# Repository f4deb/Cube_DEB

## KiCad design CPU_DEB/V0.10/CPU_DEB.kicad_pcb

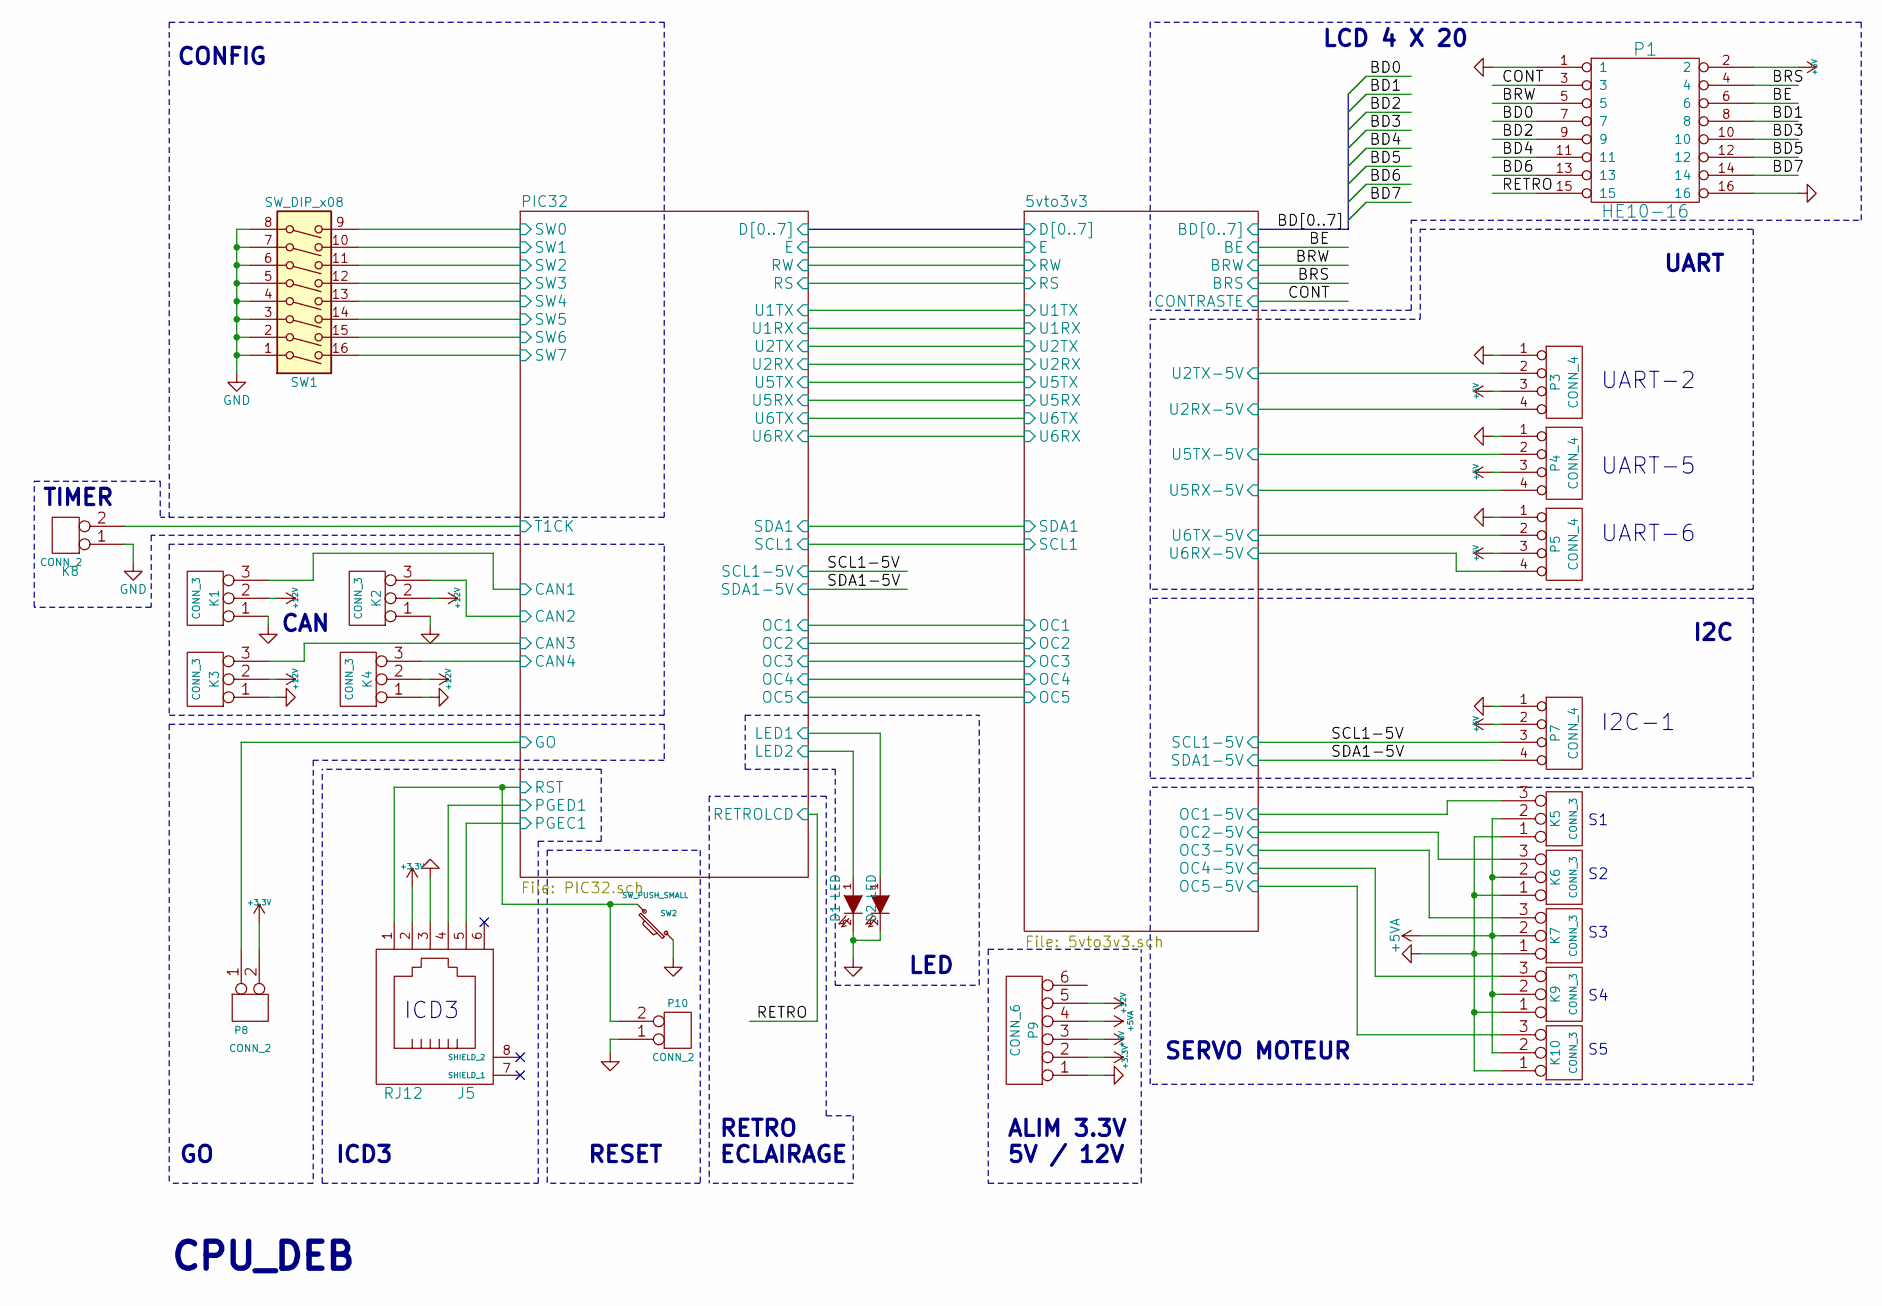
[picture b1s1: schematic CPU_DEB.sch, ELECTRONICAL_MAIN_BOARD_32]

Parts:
D1, D2: LED; LED_0603
J5: RJ12
K1, K2, K3, K4: CONN_3; KK-3
K5, K6, K7, K9, K10: CONN_3; KK-3-H
K8: CONN_2; KK-2-H
P1: HE10-16; he10-16d
P3: CONN_4; Molex_KK_6410-04
P4, P5, P7: CONN_4; KK-4-H
P8, P10: CONN_2; KK-2-H
P9: CONN_6; KK-6-H
SW1: SW_DIP_x08; SW_DIP_x8_Piano
SW2: SW_PUSH_SMALL; SW

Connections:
+3V3: J5.2, P8.2 (PM), P9.2; also elsewhere on the board
+5V: P1.2, P3.3, P4.3, P5.3, P7.2, P9.3; also elsewhere on the board
+5VA: K5.2 (PM), K6.2 (PM), K7.2 (PM), K9.2 (PM), K10.2 (PM), P9.4; also elsewhere on the board
+12V: K1.2 (PM), K2.2 (PM), K3.2 (PM), K4.2 (PM), P9.5
/5vto3v3/OC1-5V: K5.3; also elsewhere on the board
/5vto3v3/OC2-5V: K6.3; also elsewhere on the board
/5vto3v3/OC3-5V: K7.3; also elsewhere on the board
/5vto3v3/OC4-5V: K9.3; also elsewhere on the board
/5vto3v3/OC5-5V: K10.3; also elsewhere on the board
/5vto3v3/U2RX-5V: P3.4; also elsewhere on the board
/5vto3v3/U2TX-5V: P3.2; also elsewhere on the board
/5vto3v3/U5RX-5V: P4.4; also elsewhere on the board
/5vto3v3/U5TX-5V: P4.2; also elsewhere on the board
/5vto3v3/U6RX-5V: P5.4; also elsewhere on the board
/5vto3v3/U6TX-5V: P5.2; also elsewhere on the board
/BD0: P1.7; also elsewhere on the board
/BD1: P1.8; also elsewhere on the board
/BD2: P1.9; also elsewhere on the board
/BD3: P1.10; also elsewhere on the board
/BD4: P1.11; also elsewhere on the board
/BD5: P1.12; also elsewhere on the board
/BD6: P1.13; also elsewhere on the board
/BD7: P1.14; also elsewhere on the board
/BE: P1.6; also elsewhere on the board
/BRS: P1.4; also elsewhere on the board
/BRW: P1.5; also elsewhere on the board
/CONT: P1.3; also elsewhere on the board
/PIC32/CAN1: K1.3; also elsewhere on the board
/PIC32/CAN2: K2.3; also elsewhere on the board
/PIC32/CAN3: K3.3; also elsewhere on the board
/PIC32/CAN4: K4.3; also elsewhere on the board
/PIC32/GO: P8.1; also elsewhere on the board
/PIC32/LED1: D2.1 (A); also elsewhere on the board
/PIC32/LED2: D1.1 (A); also elsewhere on the board
/PIC32/PGEC1: J5.5; also elsewhere on the board
/PIC32/PGED1: J5.4; also elsewhere on the board
/PIC32/RST: J5.1, P10.2 (PM), SW2.2; also elsewhere on the board
/PIC32/SW0: SW1.9; also elsewhere on the board
/PIC32/SW1: SW1.10; also elsewhere on the board
/PIC32/SW2: SW1.11; also elsewhere on the board
/PIC32/SW3: SW1.12; also elsewhere on the board
/PIC32/SW4: SW1.13; also elsewhere on the board
/PIC32/SW5: SW1.14; also elsewhere on the board
/PIC32/SW6: SW1.15; also elsewhere on the board
/PIC32/SW7: SW1.16; also elsewhere on the board
/PIC32/T1CK: K8.2 (PM); also elsewhere on the board
/RETRO: P1.15; also elsewhere on the board
/SCL1-5V: P7.3; also elsewhere on the board
/SDA1-5V: P7.4; also elsewhere on the board
GND: D1.2 (K), D2.2 (K), J5.3, J5.7 (SHIELD_1), J5.8 (SHIELD_2), K1.1, K2.1, K3.1, K4.1, K5.1, K6.1, K7.1, K8.1, K9.1, K10.1, P1.1, P1.16, P3.1, P4.1, P5.1, P7.1, P9.1, P10.1, SW1.1, SW1.2, SW1.3, SW1.4, SW1.5, SW1.6, SW1.7, SW1.8, SW2.1; also elsewhere on the board

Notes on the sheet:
ALIM 3.3V 5V / 12V
LED
CPU_DEB
LCD 4 X 20
RESET
ICD3
CAN
UART
I2C
CONFIG
SERVO MOTEUR
I2C-1
UART-6
UART-2
TIMER
RETRO ECLAIRAGE
UART-5

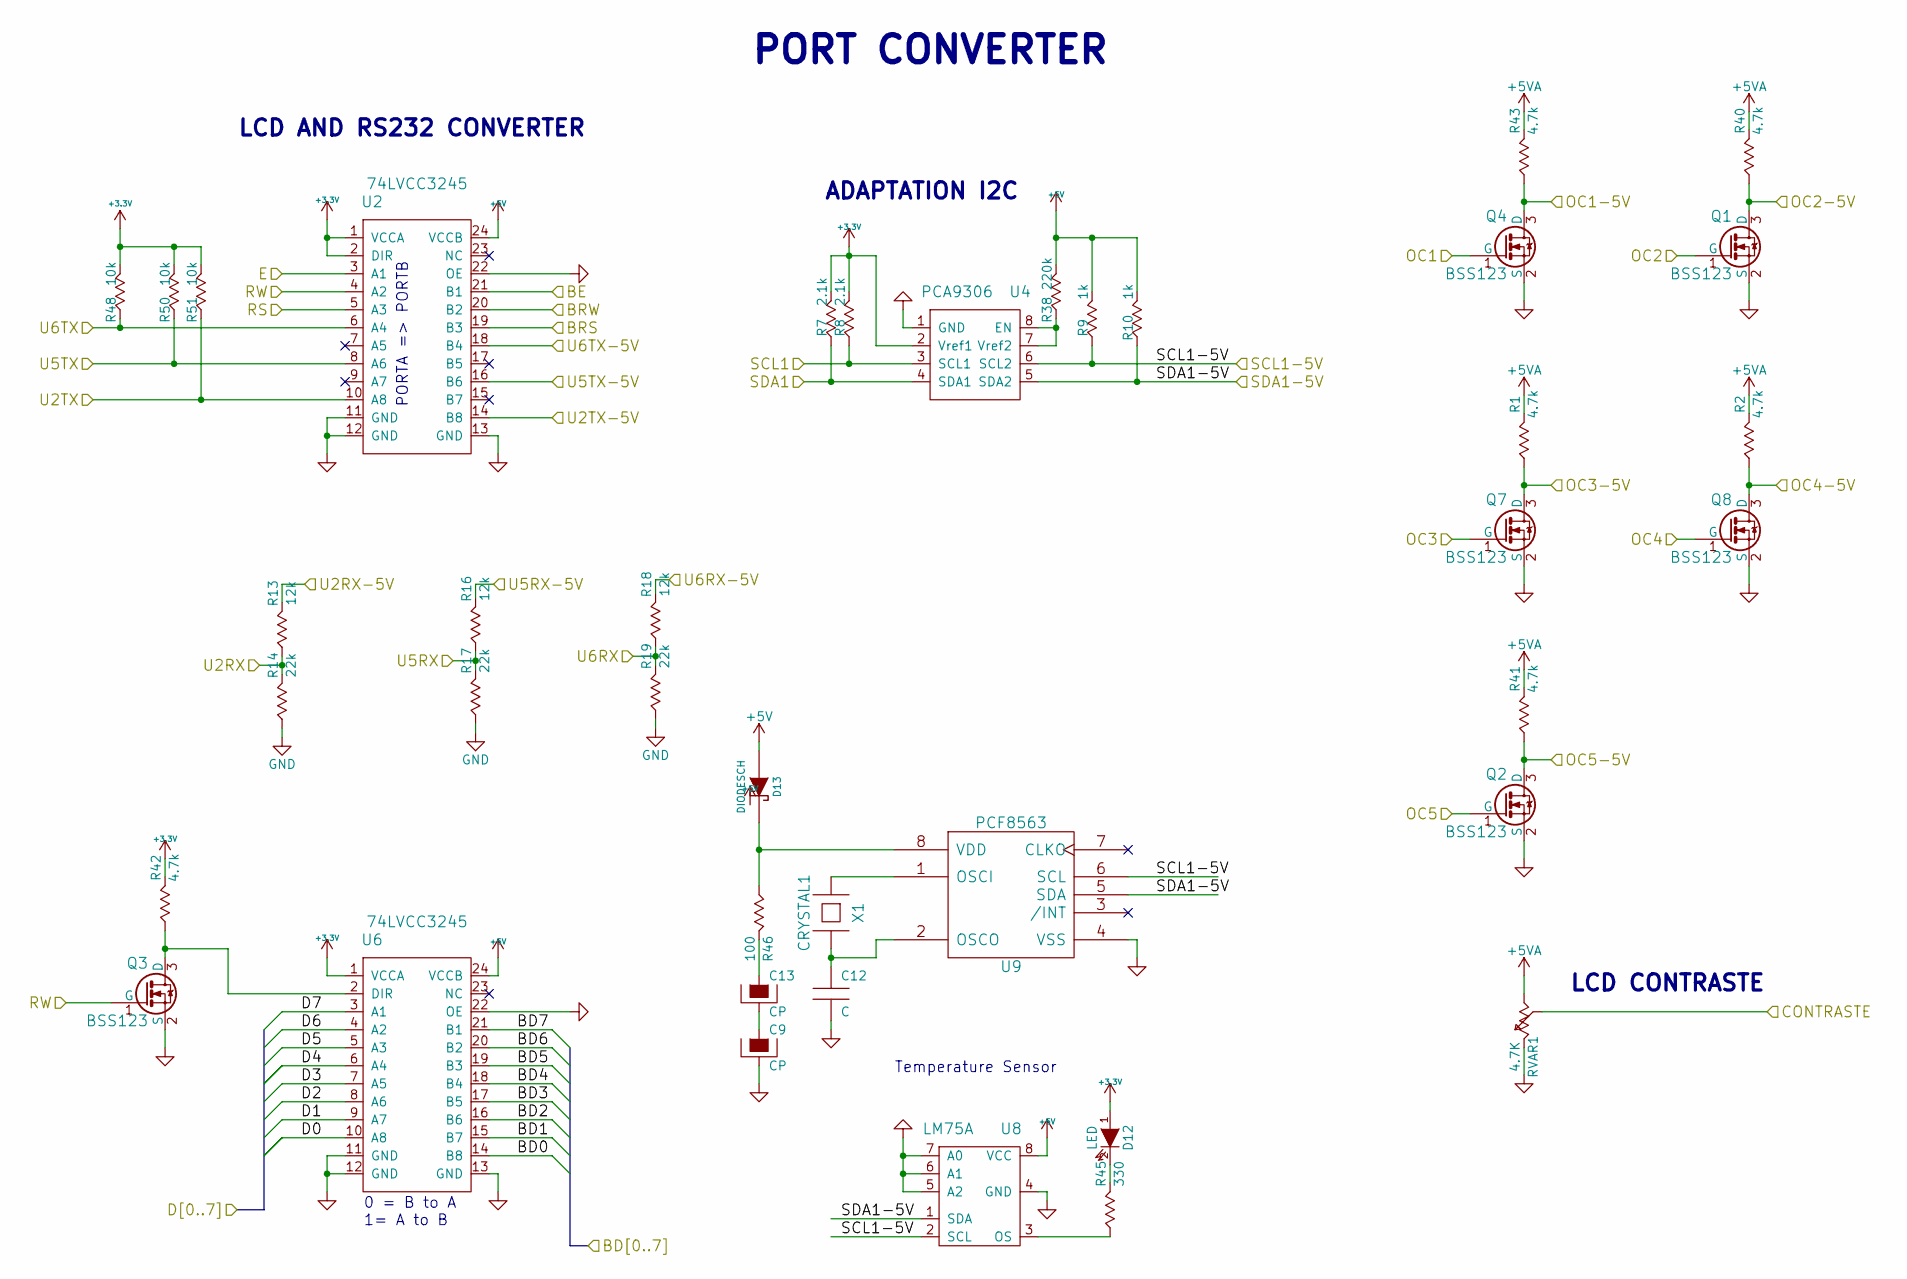
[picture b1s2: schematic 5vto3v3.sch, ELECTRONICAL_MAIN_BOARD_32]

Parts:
C9, C13: CP; C-10F
C12: C; C_0603
D12: LED; LED_0603
D13: DIODESCH; SMA_Standard
Q1, Q2, Q3, Q4, Q7, Q8: BSS123; SOT-23
R1, R2, R40, R41, R42, R43: 4.7k; R_0603
R7, R8: 2.1k; R_0603
R9, R10: 1k; R_0603
R13, R16, R18: 12k; R_0603
R14, R17, R19: 22k; R_0603
R38: 220k; R_0603
R45: 330; R_0603
R46: 100; R_0603
R48, R50, R51: 10k; R_0603
RVAR1: 4.7K; POT_SMD
U2, U6: 74LVCC3245; SSOP24
U4: PCA9306; VSSOP-8
U8: LM75A; SOIC-8-N
U9: PCF8563; SOIC-8-N
X1: CRYSTAL1; MDX75104

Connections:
+3V3: D12.1 (A), R7.1, R8.1, R42.1, R48.1, R50.1, R51.1, U2.1 (VCCA), U2.2 (DIR), U4.2 (Vref1), U6.1 (VCCA); also elsewhere on the board
+5V: D13.1 (A), R9.1, R10.1, R38.1, U2.24 (VCCB), U6.24 (VCCB), U8.8 (VCC); also elsewhere on the board
+5VA: R1.1, R2.1, R40.1, R41.1, R43.1, RVAR1.3; also elsewhere on the board
/5vto3v3/D0: U6.10 (A8); also elsewhere on the board
/5vto3v3/D1: U6.9 (A7); also elsewhere on the board
/5vto3v3/D2: U6.8 (A6); also elsewhere on the board
/5vto3v3/D3: U6.7 (A5); also elsewhere on the board
/5vto3v3/D4: U6.6 (A4); also elsewhere on the board
/5vto3v3/D5: U6.5 (A3); also elsewhere on the board
/5vto3v3/D6: U6.4 (A2); also elsewhere on the board
/5vto3v3/D7: U6.3 (A1); also elsewhere on the board
/5vto3v3/E: U2.3 (A1); also elsewhere on the board
/5vto3v3/OC1: Q4.1 (G); also elsewhere on the board
/5vto3v3/OC1-5V: Q4.3 (D), R43.2; also elsewhere on the board
/5vto3v3/OC2: Q1.1 (G); also elsewhere on the board
/5vto3v3/OC2-5V: Q1.3 (D), R40.2; also elsewhere on the board
/5vto3v3/OC3: Q7.1 (G); also elsewhere on the board
/5vto3v3/OC3-5V: Q7.3 (D), R1.2; also elsewhere on the board
/5vto3v3/OC4: Q8.1 (G); also elsewhere on the board
/5vto3v3/OC4-5V: Q8.3 (D), R2.2; also elsewhere on the board
/5vto3v3/OC5: Q2.1 (G); also elsewhere on the board
/5vto3v3/OC5-5V: Q2.3 (D), R41.2; also elsewhere on the board
/5vto3v3/RS: U2.5 (A3); also elsewhere on the board
/5vto3v3/RW: Q3.1 (G), U2.4 (A2); also elsewhere on the board
/5vto3v3/SCL1: R8.2, U4.3 (SCL1); also elsewhere on the board
/5vto3v3/SDA1: R7.2, U4.4 (SDA1); also elsewhere on the board
/5vto3v3/U2RX: R13.2, R14.1; also elsewhere on the board
/5vto3v3/U2RX-5V: R13.1; also elsewhere on the board
/5vto3v3/U2TX: R51.2, U2.10 (A8); also elsewhere on the board
/5vto3v3/U2TX-5V: U2.14 (B8); also elsewhere on the board
/5vto3v3/U5RX: R16.2, R17.1; also elsewhere on the board
/5vto3v3/U5RX-5V: R16.1; also elsewhere on the board
/5vto3v3/U5TX: R50.2, U2.8 (A6); also elsewhere on the board
/5vto3v3/U5TX-5V: U2.16 (B6); also elsewhere on the board
/5vto3v3/U6RX: R18.2, R19.1; also elsewhere on the board
/5vto3v3/U6RX-5V: R18.1; also elsewhere on the board
/5vto3v3/U6TX: R48.2, U2.6 (A4); also elsewhere on the board
/5vto3v3/U6TX-5V: U2.18 (B4); also elsewhere on the board
/BD0: U6.14 (B8); also elsewhere on the board
/BD1: U6.15 (B7); also elsewhere on the board
/BD2: U6.16 (B6); also elsewhere on the board
/BD3: U6.17 (B5); also elsewhere on the board
/BD4: U6.18 (B4); also elsewhere on the board
/BD5: U6.19 (B3); also elsewhere on the board
/BD6: U6.20 (B2); also elsewhere on the board
/BD7: U6.21 (B1); also elsewhere on the board
/BE: U2.21 (B1); also elsewhere on the board
/BRS: U2.19 (B3); also elsewhere on the board
/BRW: U2.20 (B2); also elsewhere on the board
/CONT: RVAR1.2; also elsewhere on the board
/SCL1-5V: R9.2, U4.6 (SCL2), U8.2 (SCL), U9.6 (SCL); also elsewhere on the board
/SDA1-5V: R10.2, U4.5 (SDA2), U8.1 (SDA), U9.5 (SDA); also elsewhere on the board
GND: C9.2, C12.2, Q1.2 (S), Q2.2 (S), Q3.2 (S), Q4.2 (S), Q7.2 (S), Q8.2 (S), R14.2, R17.2, R19.2, RVAR1.1, U2.11 (GND), U2.12 (GND), U2.13 (GND), U2.22 (OE), U4.1 (GND), U6.11 (GND), U6.12 (GND), U6.13 (GND), U6.22 (OE), U8.4 (GND), U8.5 (A2), U8.6 (A1), U8.7 (A0), U9.4 (VSS); also elsewhere on the board
unnamed: C12.1, U9.2 (OSCO), X1.2
unnamed: C13.1, R46.1
unnamed: C9.1, C13.2
unnamed: D12.2 (K), R45.1
unnamed: D13.2 (K), R46.2, U9.8 (VDD)
unnamed: Q3.3 (D), R42.2, U6.2 (DIR)
unnamed: R38.2, U4.7 (Vref2), U4.8 (EN)
unnamed: R45.2, U8.3 (OS)
unnamed: U9.1 (OSCI), X1.1

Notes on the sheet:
ADAPTATION I2C
PORTA => PORTB
0 = B to A 1= A to B
LCD AND RS232 CONVERTER
PORT CONVERTER
Temperature Sensor
LCD CONTRASTE

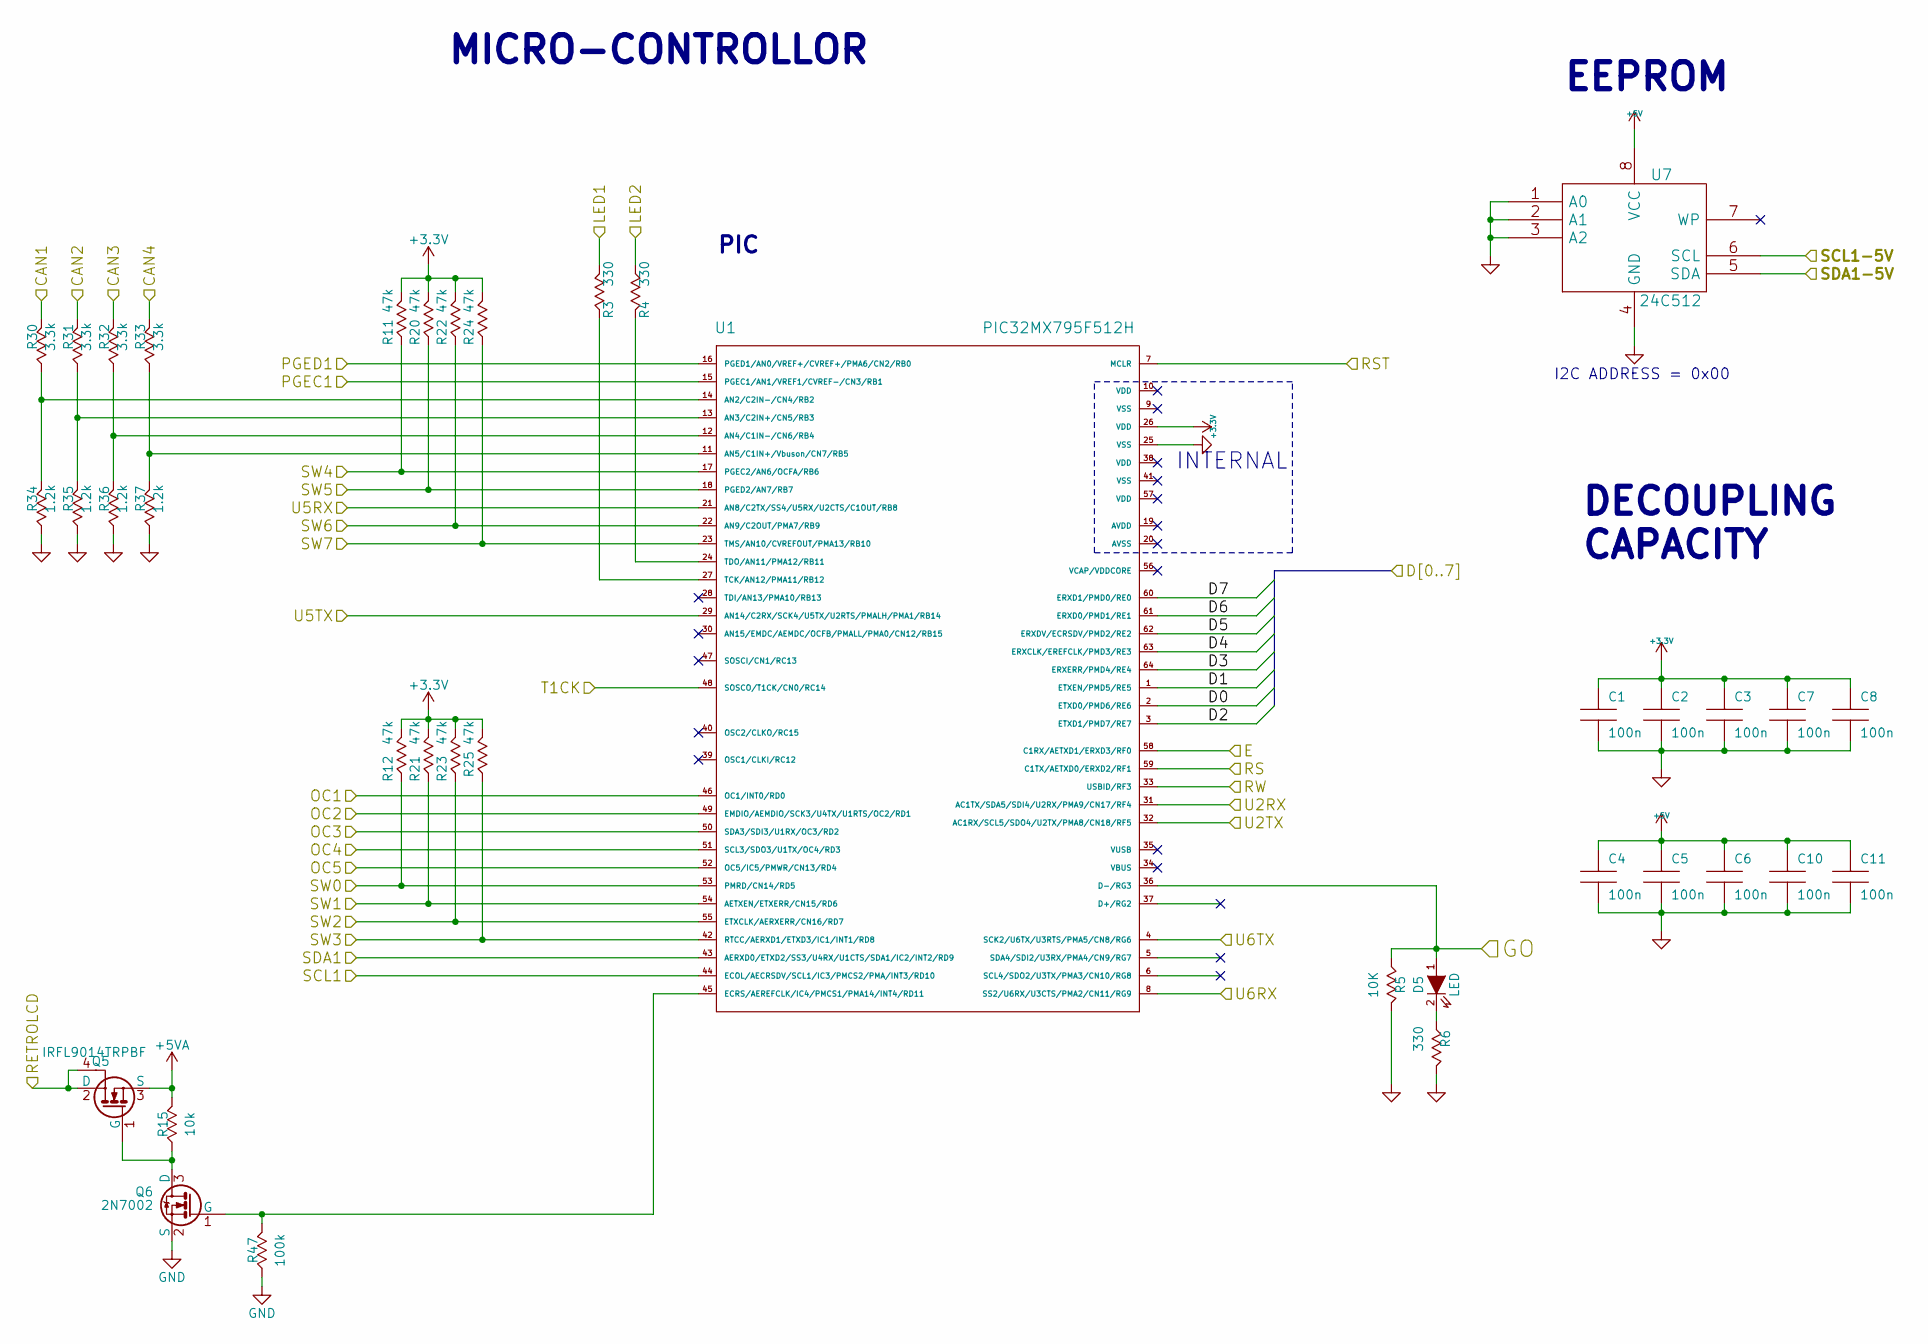
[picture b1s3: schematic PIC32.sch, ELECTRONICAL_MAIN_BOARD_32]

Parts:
C1, C2, C3, C4, C5, C6, C7, C8: 100n; C_0603
C10, C11: 100n; C_0603_HandSoldering
D5: LED; LED_0603
Q5: IRFL9014TRPBF; SOT-223
Q6: 2N7002; SOT-23
R3, R4, R6: 330; R_0603
R5: 10K; R_0603
R11, R12, R20, R21, R22, R23, R24, R25: 47k; SM0603_Resistor
R15: 10k; R_0603
R30, R31, R32, R33: 3.3k; R_0603
R34, R35, R36, R37: 1.2k; R_0603
R47: 100k; R_0603
U1: PIC32MX795F512H; PIC32_64
U7: 24C512; SOIC-8-N

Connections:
+3V3: C1.1, C2.1, C3.1, C7.1, C8.1, R11.1, R12.1, R20.1, R21.1, R22.1, R23.1, R24.1, R25.1, U1.26 (VDD); also elsewhere on the board
+5V: C4.1, C5.1, C6.1, C10.1, C11.1, U7.8 (VCC); also elsewhere on the board
+5VA: Q5.3 (S), R15.1; also elsewhere on the board
/5vto3v3/D0: U1.2 (ETXD0/PMD6/RE6); also elsewhere on the board
/5vto3v3/D1: U1.1 (ETXEN/PMD5/RE5); also elsewhere on the board
/5vto3v3/D2: U1.3 (ETXD1/PMD7/RE7); also elsewhere on the board
/5vto3v3/D3: U1.64 (ERXERR/PMD4/RE4); also elsewhere on the board
/5vto3v3/D4: U1.63 (ERXCLK/EREFCLK/PMD3/RE3); also elsewhere on the board
/5vto3v3/D5: U1.62 (ERXDV/ECRSDV/PMD2/RE2); also elsewhere on the board
/5vto3v3/D6: U1.61 (ERXD0/PMD1/RE1); also elsewhere on the board
/5vto3v3/D7: U1.60 (ERXD1/PMD0/RE0); also elsewhere on the board
/5vto3v3/E: U1.58 (C1RX/AETXD1/ERXD3/RF0); also elsewhere on the board
/5vto3v3/OC1: U1.46 (OC1/INT0/RD0); also elsewhere on the board
/5vto3v3/OC2: U1.49 (EMDIO/AEMDIO/SCK3/U4TX/U1RTS/OC2/RD1); also elsewhere on the board
/5vto3v3/OC3: U1.50 (SDA3/SDI3/U1RX/OC3/RD2); also elsewhere on the board
/5vto3v3/OC4: U1.51 (SCL3/SDO3/U1TX/OC4/RD3); also elsewhere on the board
/5vto3v3/OC5: U1.52 (OC5/IC5/PMWR/CN13/RD4); also elsewhere on the board
/5vto3v3/RS: U1.59 (C1TX/AETXD0/ERXD2/RF1); also elsewhere on the board
/5vto3v3/RW: U1.33 (USBID/RF3); also elsewhere on the board
/5vto3v3/SCL1: U1.44 (ECOL/AECRSDV/SCL1/IC3/PMCS2/PMA/INT3/RD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); also elsewhere on the board
/5vto3v3/SDA1: U1.43 (AERXD0/ETXD2/SS3/U4RX/U1CTS/SDA1/IC2/IN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); also elsewhere on the board
/5vto3v3/U2RX: U1.31 (AC1TX/SDA5/SDI4/U2RX/PMA9/CN17/RF4); also elsewhere on the board
/5vto3v3/U2TX: U1.32 (AC1RX/SCL5/SDO4/U2TX/PMA8/CN18/RF5); also elsewhere on the board
/5vto3v3/U5RX: U1.21 (AN8/C2TX/SS4/U5RX/U2CTS/C1OUT/RB8); also elsewhere on the board
/5vto3v3/U5TX: U1.29 (AN14/C2RX/SCK4/U5TX/U2RTS/PMALH/PMA1/RB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); also elsewhere on the board
/5vto3v3/U6RX: U1.8 (SS2/U6RX/U3CTS/PMA2/CN11/RG9); also elsewhere on the board
/5vto3v3/U6TX: U1.4 (SCK2/U6TX/U3RTS/PMA5/CN8/RG6); also elsewhere on the board
/PIC32/CAN1: R30.1; also elsewhere on the board
/PIC32/CAN2: R31.1; also elsewhere on the board
/PIC32/CAN3: R32.1; also elsewhere on the board
/PIC32/CAN4: R33.1; also elsewhere on the board
/PIC32/GO: D5.1 (A), R5.1, U1.36 (D-/RG3); also elsewhere on the board
/PIC32/LED1: R3.2; also elsewhere on the board
/PIC32/LED2: R4.2; also elsewhere on the board
/PIC32/PGEC1: U1.15 (PGEC1/AN1/VREF1/CVREF-/CN3/RB1); also elsewhere on the board
/PIC32/PGED1: U1.16 (PGED1/AN0/VREF+/CVREF+/PMA6/CN2/RB0); also elsewhere on the board
/PIC32/RST: U1.7 (MCLR); also elsewhere on the board
/PIC32/SW0: R12.2, U1.53 (PMRD/CN14/RD5); also elsewhere on the board
/PIC32/SW1: R21.2, U1.54 (AETXEN/ETXERR/CN15/RD6); also elsewhere on the board
/PIC32/SW2: R23.2, U1.55 (ETXCLK/AERXERR/CN16/RD7); also elsewhere on the board
/PIC32/SW3: R25.2, U1.42 (RTCC/AERXD1/ETXD3/IC1/INT1/RD8); also elsewhere on the board
/PIC32/SW4: R11.2, U1.17 (PGEC2/AN6/OCFA/RB6); also elsewhere on the board
/PIC32/SW5: R20.2, U1.18 (PGED2/AN7/RB7); also elsewhere on the board
/PIC32/SW6: R22.2, U1.22 (AN9/C2OUT/PMA7/RB9); also elsewhere on the board
/PIC32/SW7: R24.2, U1.23 (TMS/AN10/CVREFOUT/PMA13/RB10); also elsewhere on the board
/PIC32/T1CK: U1.48 (SOSCO/T1CK/CN0/RC14); also elsewhere on the board
/RETRO: Q5.2 (D), Q5.4; also elsewhere on the board
/SCL1-5V: U7.6 (SCL); also elsewhere on the board
/SDA1-5V: U7.5 (SDA); also elsewhere on the board
GND: C1.2, C2.2, C3.2, C4.2, C5.2, C6.2, C7.2, C8.2, C10.2, C11.2, Q6.2 (S), R5.2, R6.2, R34.2, R35.2, R36.2, R37.2, R47.2, U1.25 (VSS), U7.1 (A0), U7.2 (A1), U7.3 (A2), U7.4 (GND); also elsewhere on the board
unnamed: D5.2 (K), R6.1
unnamed: Q5.1 (G), Q6.3 (D), R15.2
unnamed: Q6.1 (G), R47.1, U1.45 (ECRS/AEREFCLK/IC4/PMCS1/PMA14/INT4/RD11)
unnamed: R3.1, U1.27 (TCK/AN12/PMA11/RB12)
unnamed: R4.1, U1.24 (TDO/AN11/PMA12/RB11)
unnamed: R30.2, R34.1, U1.14 (AN2/C2IN-/CN4/RB2)
unnamed: R31.2, R35.1, U1.13 (AN3/C2IN+/CN5/RB3)
unnamed: R32.2, R36.1, U1.12 (AN4/C1IN-/CN6/RB4)
unnamed: R33.2, R37.1, U1.11 (AN5/C1IN+/Vbuson/CN7/RB5)

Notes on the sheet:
INTERNAL
MICRO-CONTROLLOR
PIC
DECOUPLING CAPACITY
EEPROM
I2C ADDRESS = 0x00

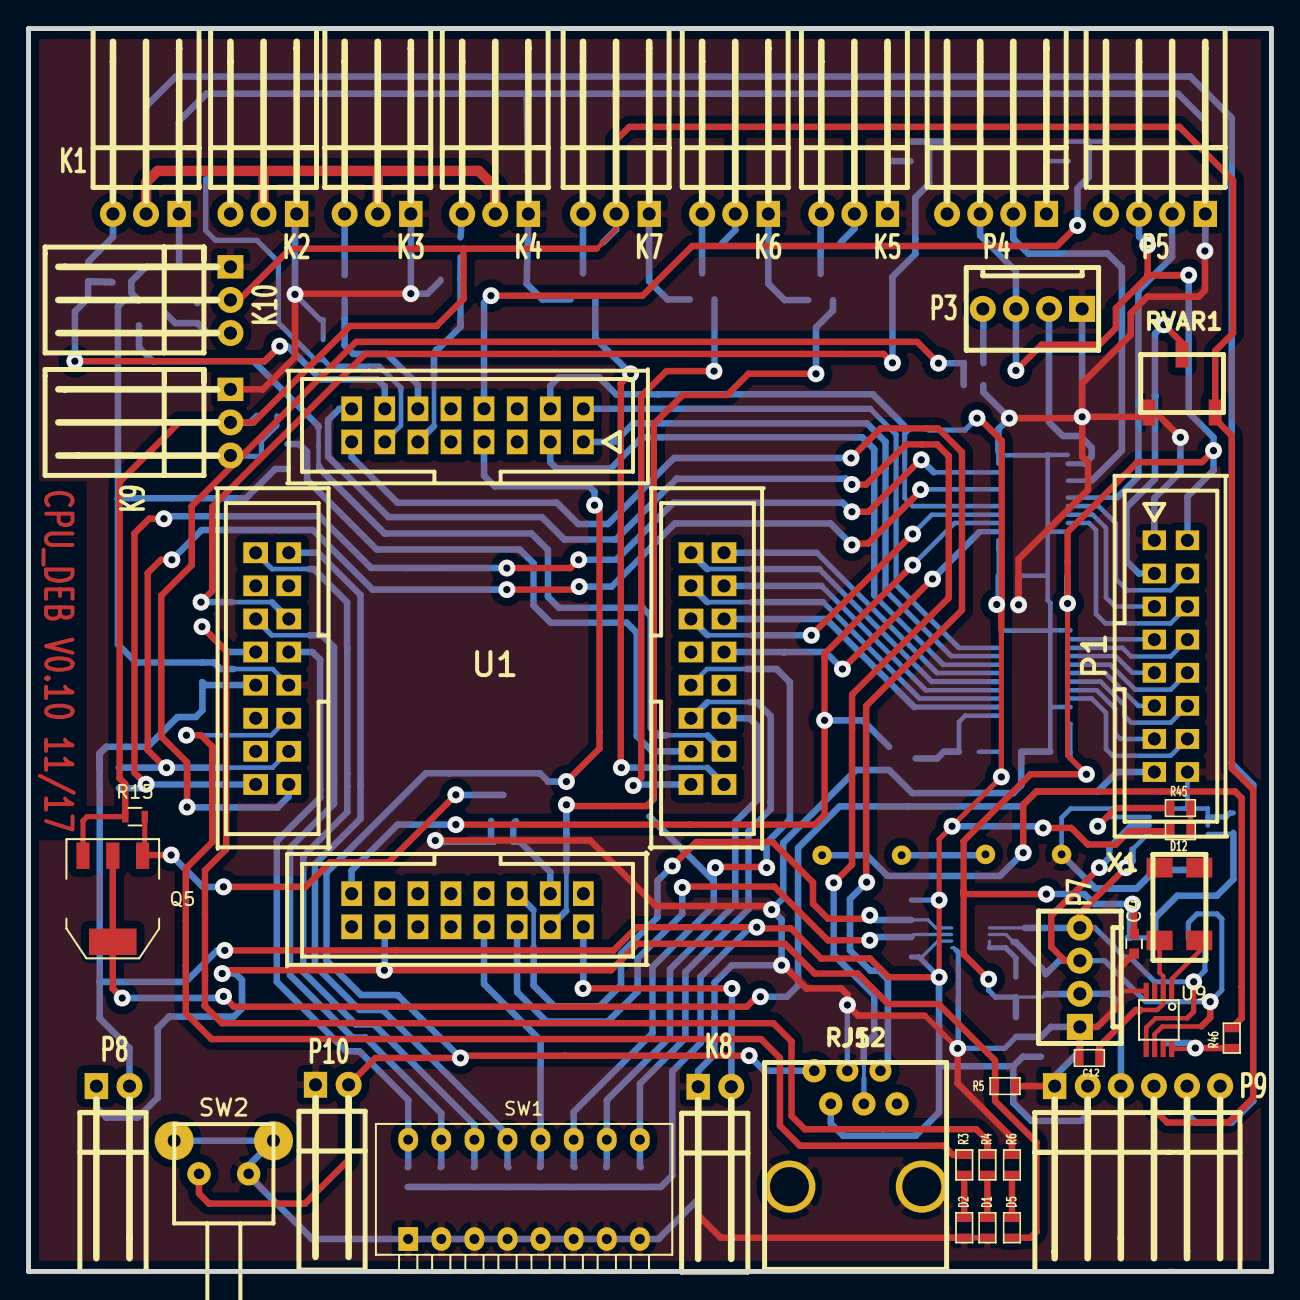
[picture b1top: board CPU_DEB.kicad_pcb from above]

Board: 2 copper layers, 95.4 x 95.4 mm, 100 parts (0 on the bottom side), 92 nets.

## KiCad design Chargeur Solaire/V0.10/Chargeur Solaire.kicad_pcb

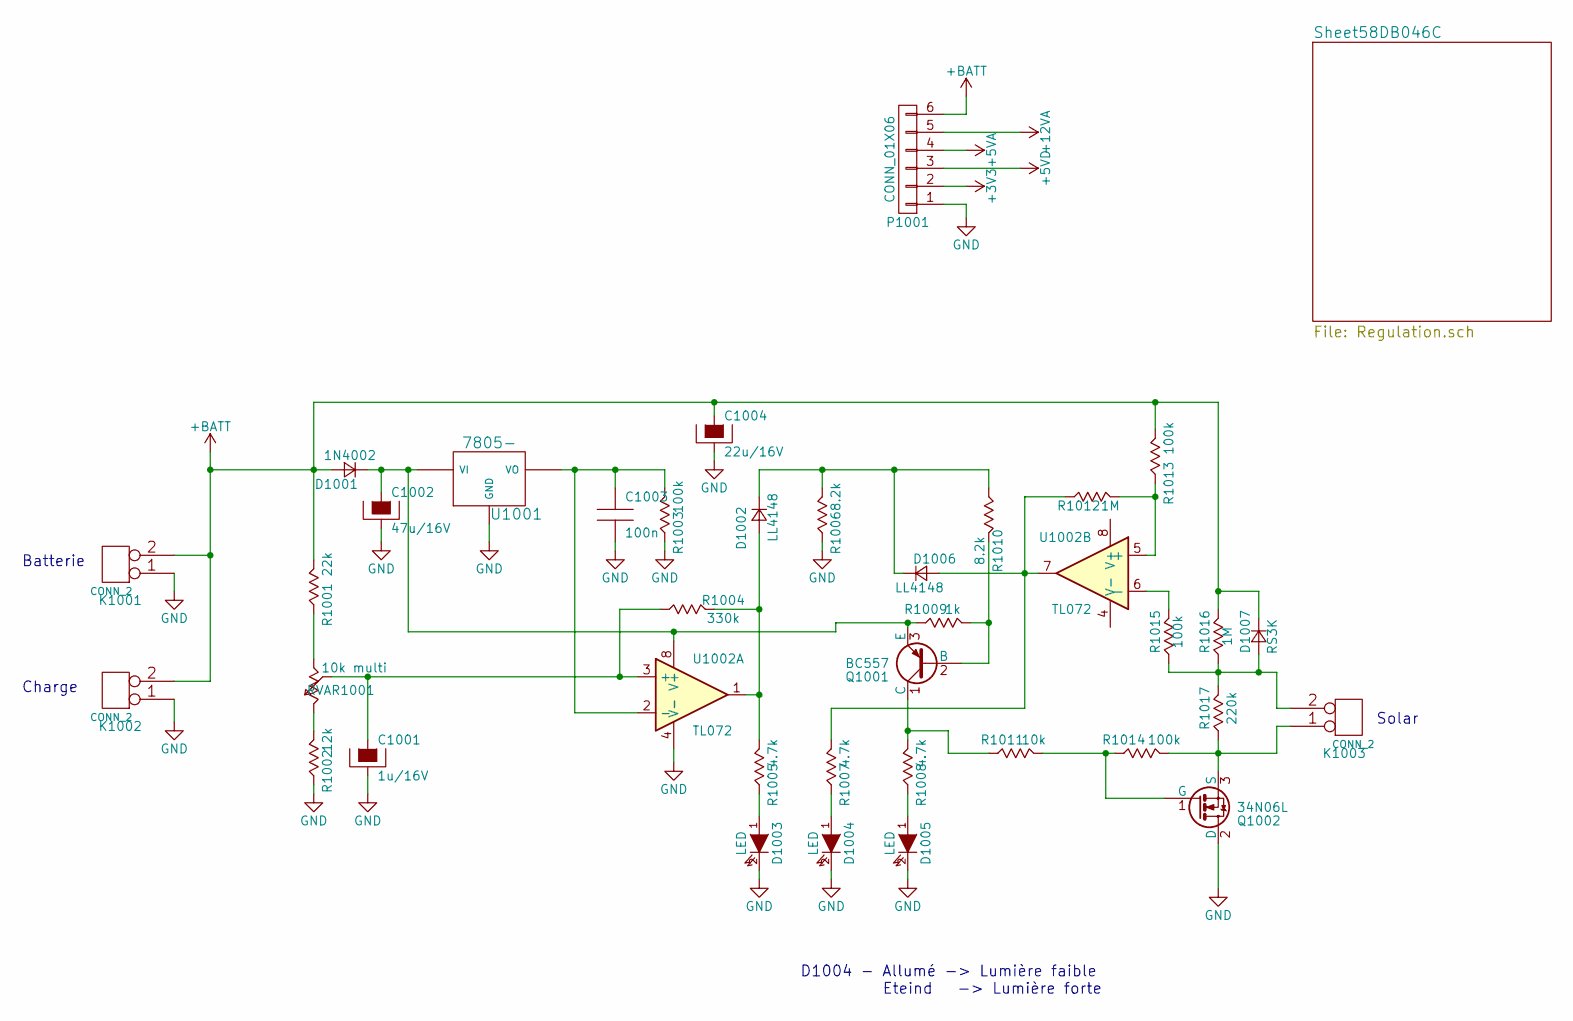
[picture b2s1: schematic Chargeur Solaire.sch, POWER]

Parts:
C1001: 1u/16V; Tantalum_Case-A_EIA-3216-18_Hand
C1002: 47u/16V; Tantalum_Case-B_EIA-3528-21_Hand
C1003: 100n; C_0603
C1004: 22u/16V; Tantalum_Case-B_EIA-3528-21_Hand
D1001: 1N4002; SMC_Handsoldering
D1002, D1006: LL4148; MiniMELF_Standard
D1003, D1004, D1005: LED; LED_0603
D1007: RS3K; SMC_Standard
K1001, K1002, K1003: CONN_2; PhoenixContact_MC-GF_02x3.50mm_Angled_ThreadedFlange_MountH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
P1001: CONN_01X06; KK-6-H
Q1001: BC557; SOT-23
Q1002: 34N06L; TO-263-3Lead
R1001: 22k; R_0603
R1002: 12k; R_0603
R1003, R1013, R1014, R1015: 100k; R_0603
R1004: 330k; R_0603
R1005, R1007, R1008: 4.7k; R_0603
R1006, R1010: 8.2k; R_0603
R1009: 1k; R_0603
R1011: 10k; R_0603
R1012, R1016: 1M; R_0603
R1017: 220k; R_0603
RVAR1001: 10k multi; Potentiometer_Trimmer-Suntan-TSR-3386C
U1001: 7805-; TO-252-2Lead
U1002: TL072; SOIC-8-N

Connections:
+5VA: P1001.4; also elsewhere on the board
+5VD: P1001.3; also elsewhere on the board
+12VA: P1001.5; also elsewhere on the board
+BATT: C1004.1, D1001.2 (A), D1007.1 (K), K1001.2 (PM), K1002.2 (PM), P1001.6, R1001.1, R1013.1, R1016.1; also elsewhere on the board
GND: C1001.2, C1002.2, C1003.2, C1004.2, D1003.2 (K), D1004.2 (K), D1005.2 (K), K1001.1, K1002.1, P1001.1, Q1002.2 (D), R1002.2, R1003.2, R1006.2, U1001.2 (GND), U1002.4 (V-); also elsewhere on the board
unnamed: C1001.1, R1004.2, RVAR1001.2, U1002.3 (+)
unnamed: C1002.1, D1001.1 (K), Q1001.3 (E), R1009.2, U1001.1 (VI), U1002.8 (V+)
unnamed: C1003.1, R1003.1, U1001.3 (VO), U1002.2 (-)
unnamed: D1002.1 (K), D1006.1 (K), R1006.1, R1010.2
unnamed: D1002.2 (A), R1004.1, R1005.1, U1002.1
unnamed: D1003.1 (A), R1005.2
unnamed: D1004.1 (A), R1007.2
unnamed: D1005.1 (A), R1008.2
unnamed: D1006.2 (A), R1007.1, R1012.2, U1002.7
unnamed: D1007.2 (A), K1003.2 (PM), R1015.2, R1016.2, R1017.1
unnamed: K1003.1, Q1002.3 (S), R1014.1, R1017.2
unnamed: Q1001.1 (C), R1008.1, R1011.2
unnamed: Q1001.2 (B), R1009.1, R1010.1
unnamed: Q1002.1 (G), R1011.1, R1014.2
unnamed: R1001.2, RVAR1001.3
unnamed: R1002.1, RVAR1001.1
unnamed: R1012.1, R1013.2, U1002.5 (+)
unnamed: R1015.1, U1002.6 (-)

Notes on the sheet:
Batterie
Charge
Solar
D1004 - Allumé -> Lumière faible Eteind -> Lumière forte
